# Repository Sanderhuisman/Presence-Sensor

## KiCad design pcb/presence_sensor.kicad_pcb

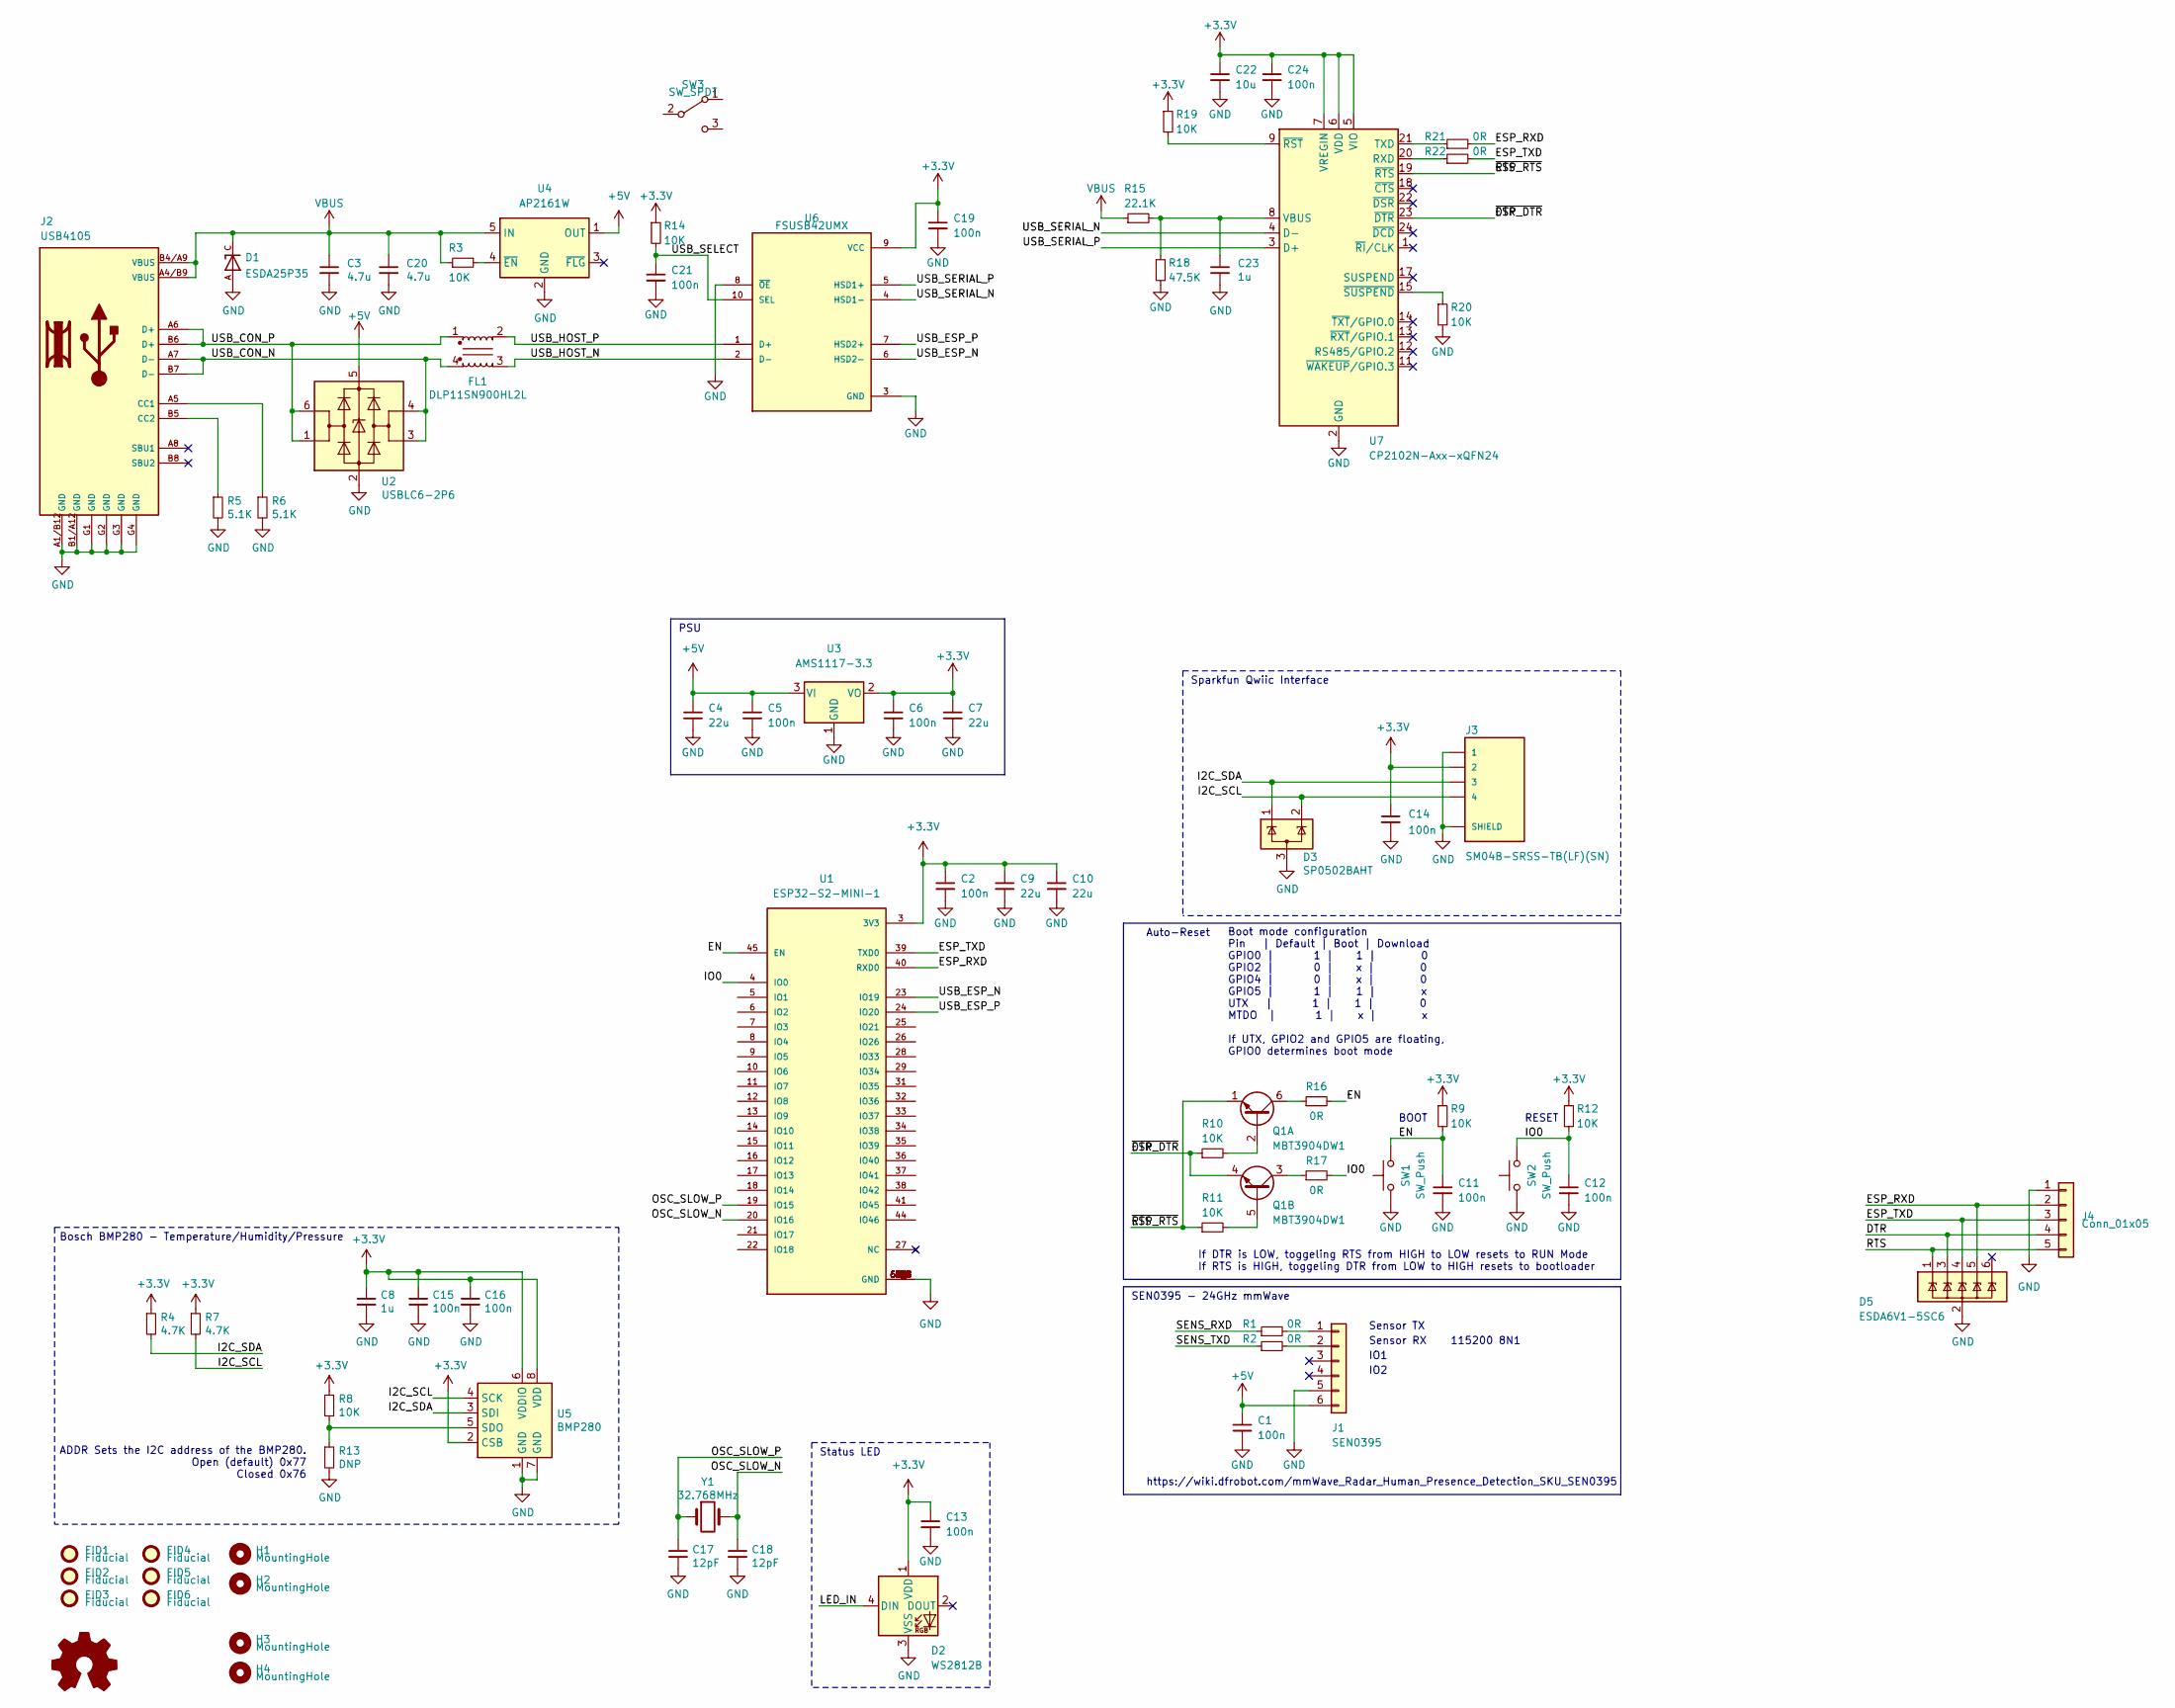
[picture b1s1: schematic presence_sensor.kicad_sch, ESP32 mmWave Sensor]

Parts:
C1, C2, C5, C6, C11, C12, C13, C14, C15, C16, C19, C21, C24: 100n; C_0603_1608Metric
C3, C20: 4.7u; C_0805_2012Metric
C4, C7, C9, C10: 22u; C_0805_2012Metric
C8, C23: 1u; C_0603_1608Metric
C17, C18: 12pF; C_0603_1608Metric
C22: 10u; C_0805_2012Metric
D1: ESDA25P35; TVS_ESDA25P35-1U1M
D2: WS2812B; LED_WS2812B_PLCC4_5.0x5.0mm_P3.2mm
D3: SP0502BAHT; SOT-23
D5: ESDA6V1-5SC6; SOT-23-6
FID1, FID2, FID3, FID4, FID5, FID6: Fiducial; Fiducial_0.5mm_Mask1mm
FL1: DLP11SN900HL2L; FIL_DLP11SN900HL2L; PARTREV N/A
H1, H2: MountingHole; MountingHole_2.7mm_M2.5
H3, H4: MountingHole; MountingHole_2.2mm_M2
J1: SEN0395; PinHeader_1x06_P2.54mm_Vertical
J2: USB4105; GCT_USB4105_REVA; PARTREV 0.2
J3: SM04B-SRSS-TB(LF)(SN); JST_SM04B-SRSS-TB(LF)(SN)
J4: Conn_01x05; PinHeader_1x05_P2.54mm_Vertical
Q1: MBT3904DW1; SOT-363_SC-70-6
R1, R2, R16, R17, R21, R22: 0R; R_0603_1608Metric
R3, R8, R9, R10, R11, R12, R14, R19, R20: 10K; R_0603_1608Metric
R4, R7: 4.7K; R_0603_1608Metric
R5, R6: 5.1K; R_0603_1608Metric
R13: DNP; R_0603_1608Metric
R15: 22.1K; R_0603_1608Metric
R18: 47.5K; R_0603_1608Metric
SW1, SW2: SW_Push; SW_Push_SPST_NO_Alps_SKRK
SW3: SW_SPDT; SW_Push_1P1T-SH_NO_CK_KMR2xxG
U1: ESP32-S2-MINI-1; XCVR_ESP32-S2-MINI-1
U2: USBLC6-2P6; SOT-666
U3: AMS1117-3.3; SOT-223-3_TabPin2
U4: AP2161W; SOT-23-5
U5: BMP280; Bosch_LGA-8_2x2.5mm_P0.65mm_ClockwisePinNumbering
U6: FSUSB42UMX; IC_FSUSB42UMX
U7: CP2102N-Axx-xQFN24; QFN-24-1EP_4x4mm_P0.5mm_EP2.6x2.6mm
Y1: 32.768MHz; NX3215SA; Part Number NX3215SA-32.768K-STD-MUA-8

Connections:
+3V3: C2.1, C6.1, C7.1, C8.1, C9.1, C10.1, C13.1, C14.1, C15.1, C16.1, C19.1, C22.1, C24.1, D2.1 (VDD), J3.2, R4.1, R7.1, R8.1, R9.1, R12.1, R14.1, R19.1, U1.3 (3V3), U3.2 (VO), U5.2 (CSB), U5.6 (VDDIO), U5.8 (VDD), U6.9 (VCC), U7.5 (VIO), U7.6 (VDD), U7.7 (VREGIN)
+5V: C1.1, C4.1, C5.1, J1.6, U2.5 (VBUS), U3.3 (VI), U4.1 (OUT)
/DTR: D5.3 (IO2), J4.4, Q1.4 (E2), R10.1, U7.23 (~DTR)
/EN: C11.1, R9.2, R16.2, SW1.2, U1.45 (EN)
/ESP_RXD: D5.5 (IO4), J4.2, R21.2, U1.40 (RXD0)
/ESP_TXD: D5.4 (IO3), J4.3, R22.2, U1.39 (TXD0)
/I2C_SCL: D3.2 (K), J3.4, R7.2, U5.4 (SCK)
/I2C_SDA: D3.1 (K), J3.3, R4.2, U5.3 (SDI)
/IO0: C12.1, R12.2, R17.2, SW2.2, U1.4 (IO0)
/LED_IN: D2.4 (DIN)
/OSC_SLOW_N: C18.1, U1.20 (IO16), Y1.2
/OSC_SLOW_P: C17.1, U1.19 (IO15), Y1.1
/RTS: D5.1 (IO1), J4.5, Q1.1 (E1), R11.1, U7.19 (~RTS)
/SENS_RXD: R1.1
/SENS_TXD: R2.1
/USB_CON_N: FL1.4, J2.A7 (D-), J2.B7 (D-), U2.3 (I/O2), U2.4 (I/O2)
/USB_CON_P: FL1.1, J2.A6 (D+), J2.B6 (D+), U2.1 (I/O1), U2.6 (I/O1)
/USB_ESP_N: U1.23 (IO19), U6.6 (HSD2-)
/USB_ESP_P: U1.24 (IO20), U6.7 (HSD2+)
/USB_HOST_N: FL1.3, U6.2 (D-)
/USB_HOST_P: FL1.2, U6.1 (D+)
/USB_SELECT: C21.1, R14.2, U6.10 (SEL)
/USB_SERIAL_N: U6.4 (HSD1-), U7.4 (D-)
/USB_SERIAL_P: U6.5 (HSD1+), U7.3 (D+)
GND: C1.2, C2.2, C3.2, C4.2, C5.2, C6.2, C7.2, C8.2, C9.2, C10.2, C11.2, C12.2, C13.2, C14.2, C15.2, C16.2, C17.2, C18.2, C19.2, C20.2, C21.2, C22.2, C23.2, C24.2, D1.A, D2.3 (VSS), D3.3 (A), D5.2 (GND), J1.5, J2.A1/B12 (GND), J2.B1/A12 (GND), J2.G1 (GND), J2.G2 (GND), J2.G3 (GND), J2.G4 (GND), J3.1, J3.S1 (SHIELD), J3.S2 (SHIELD), J4.1, R5.2, R6.2, R13.2, R18.2, R20.2, SW1.1, SW2.1, U1.1 (GND), U1.2 (GND), U1.30 (GND), U1.42 (GND), U1.43 (GND), U1.46 (GND), U1.47 (GND), U1.48 (GND), U1.49 (GND), U1.50 (GND), U1.51 (GND), U1.52 (GND), U1.53 (GND), U1.54 (GND), U1.55 (GND), U1.56 (GND), U1.57 (GND), U1.58 (GND), U1.59 (GND), U1.60 (GND), U1.61 (GND), U1.61_1 (GND), U1.61_2 (GND), U1.61_3 (GND), U1.61_4 (GND), U1.61_5 (GND), U1.61_6 (GND), U1.61_7 (GND), U1.61_8 (GND), U1.62 (GND), U1.63 (GND), U1.64 (GND), U1.65 (GND), U2.2 (GND), U3.1 (GND), U4.2 (GND), U5.1 (GND), U5.7 (GND), U6.3 (GND), U6.8 (~OE), U7.2 (GND), U7.25 (GND)
unnamed: J1.1, R1.2
unnamed: J1.2, R2.2
unnamed: J2.A5 (CC1), R6.1
unnamed: J2.B5 (CC2), R5.1
unnamed: Q1.2 (B1), R10.2
unnamed: Q1.6 (C1), R16.1
unnamed: Q1.5 (B2), R11.2
unnamed: Q1.3 (C2), R17.1
unnamed: R3.2, U4.4 (~EN)
unnamed: R8.2, R13.1, U5.5 (SDO)
unnamed: R22.1, U7.20 (RXD)
unnamed: R21.1, U7.21 (TXD)
unnamed: C23.1, R15.2, R18.1, U7.8 (VBUS)
unnamed: R19.2, U7.9 (~RST)
unnamed: R20.1, U7.15 (~SUSPEND)
VBUS: C3.1, C20.1, D1.C, J2.A4/B9 (VBUS), J2.B4/A9 (VBUS), R3.1, R15.1, U4.5 (IN)

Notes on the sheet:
Auto-Reset
Bosch BMP280 - Temperature/Humidity/Pressure
IO2
If DTR is LOW, toggeling RTS from HIGH to LOW resets to RUN Mode If RTS is HIGH, toggeling DTR from LOW to HIGH resets to bootloader
Status LED
IO1
https://wiki.dfrobot.com/mmWave_Radar_Human_Presence_Detection_SKU_SEN0395
RESET
SEN0395 - 24GHz mmWave
ADDR Sets the I2C address of the BMP280. Open (default) 0x77 Closed 0x76
Sensor RX
115200 8N1
Sensor TX
BOOT
PSU
Sparkfun Qwiic Interface
Boot mode configuration Pin | Default | Boot | Download GPIO0 | 1 | 1 | 0 GPIO2 | 0 | x | 0 GPIO4 | 0 | x | 0 GPIO5 | 1 | 1 | x UTX | 1 | 1 | 0 MTDO | 1 | x | x If UTX, GPIO2 and GPIO5 are floating, GPIO0 determines boot mode

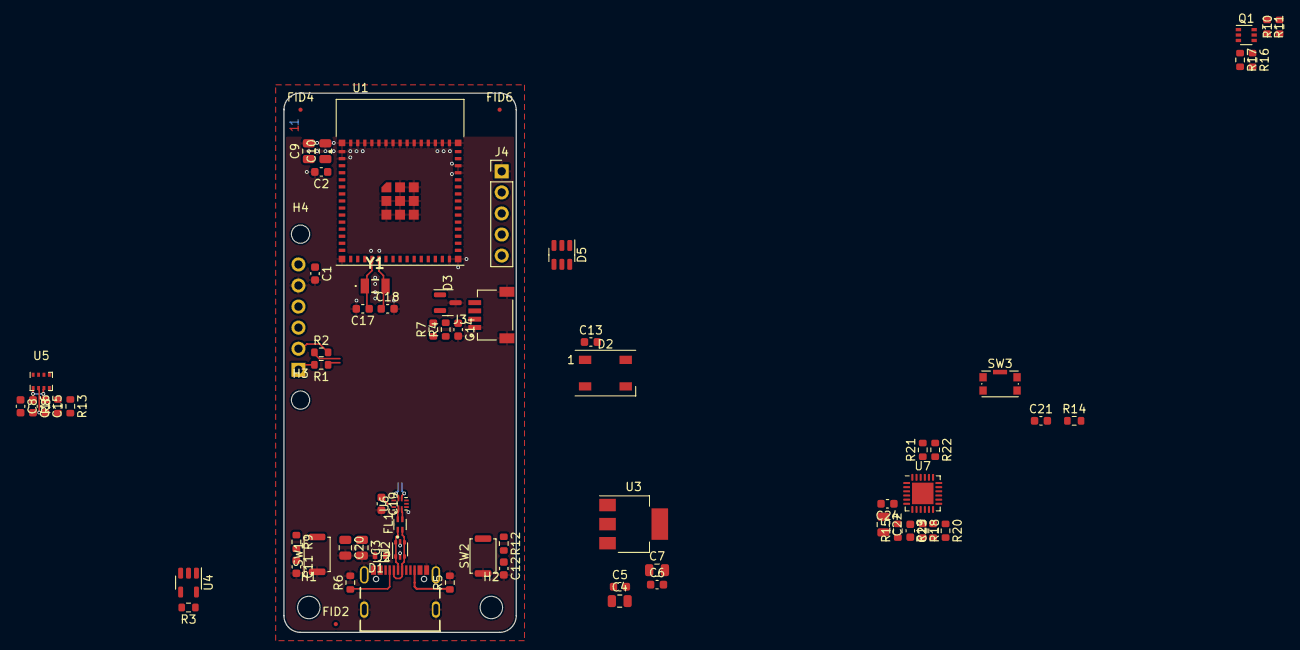
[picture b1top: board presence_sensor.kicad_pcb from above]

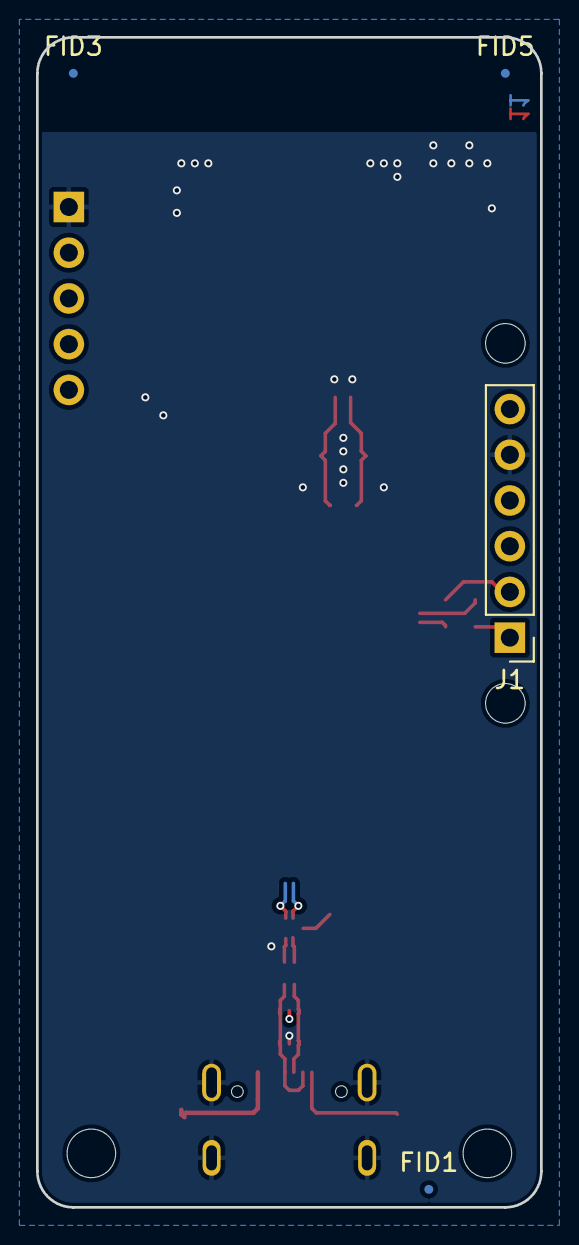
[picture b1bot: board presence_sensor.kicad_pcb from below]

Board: 2 copper layers, 28.0 x 65.0 mm, 77 parts (4 on the bottom side), 38 nets.

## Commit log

2022-01-17 Removed USB TTL
